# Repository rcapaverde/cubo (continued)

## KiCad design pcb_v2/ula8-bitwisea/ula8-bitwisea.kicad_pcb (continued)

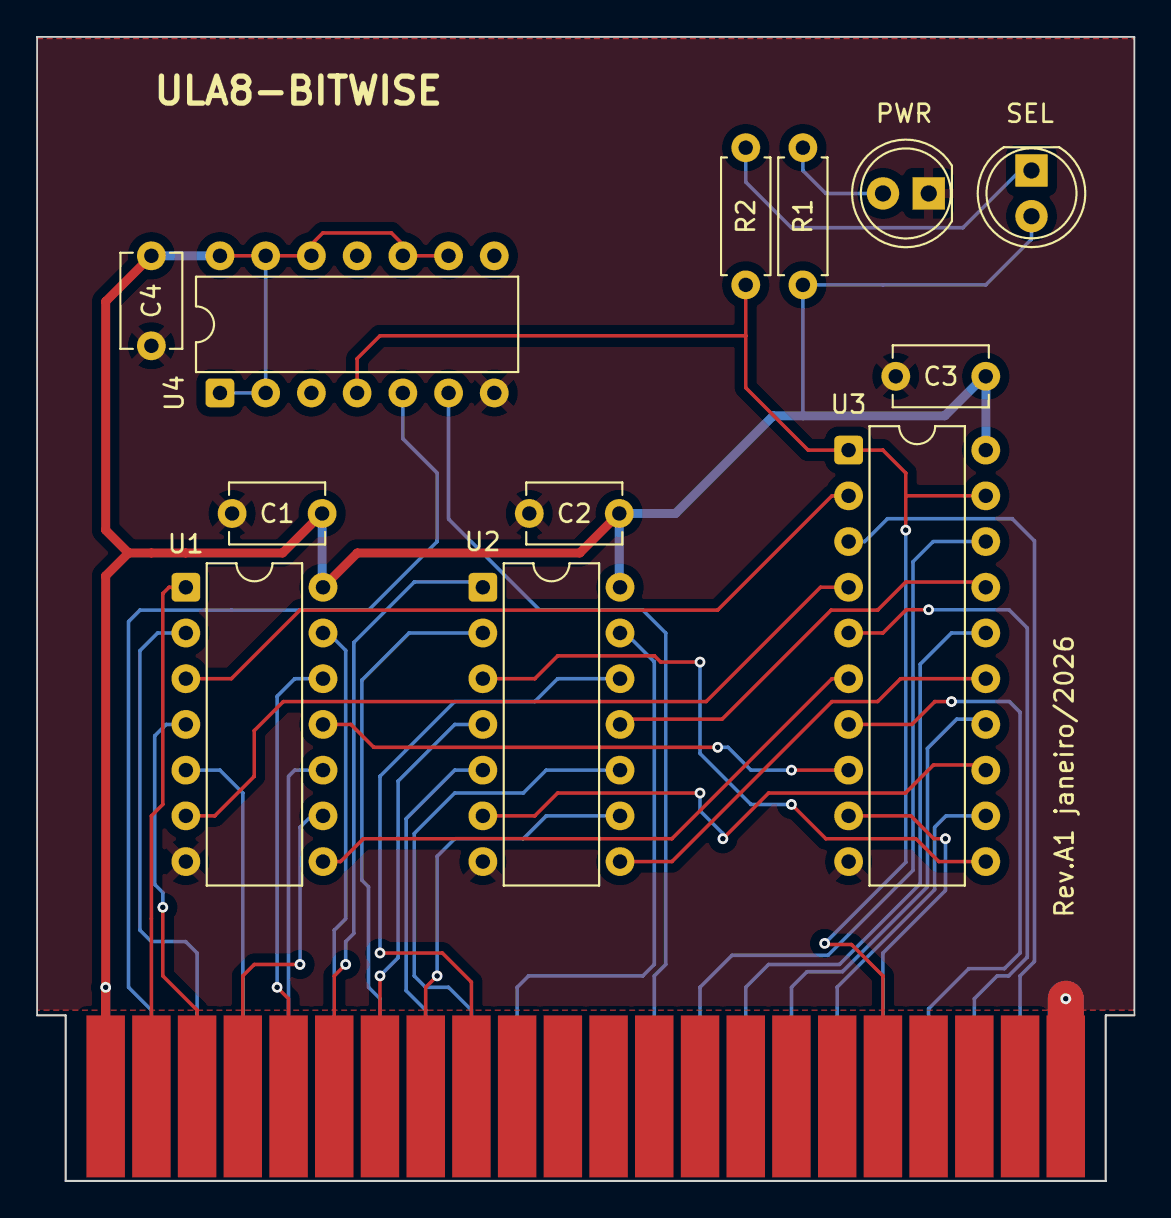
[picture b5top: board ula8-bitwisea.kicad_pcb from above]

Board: 2 copper layers, 61.0 x 63.6 mm, 13 parts (0 on the bottom side), 39 nets.

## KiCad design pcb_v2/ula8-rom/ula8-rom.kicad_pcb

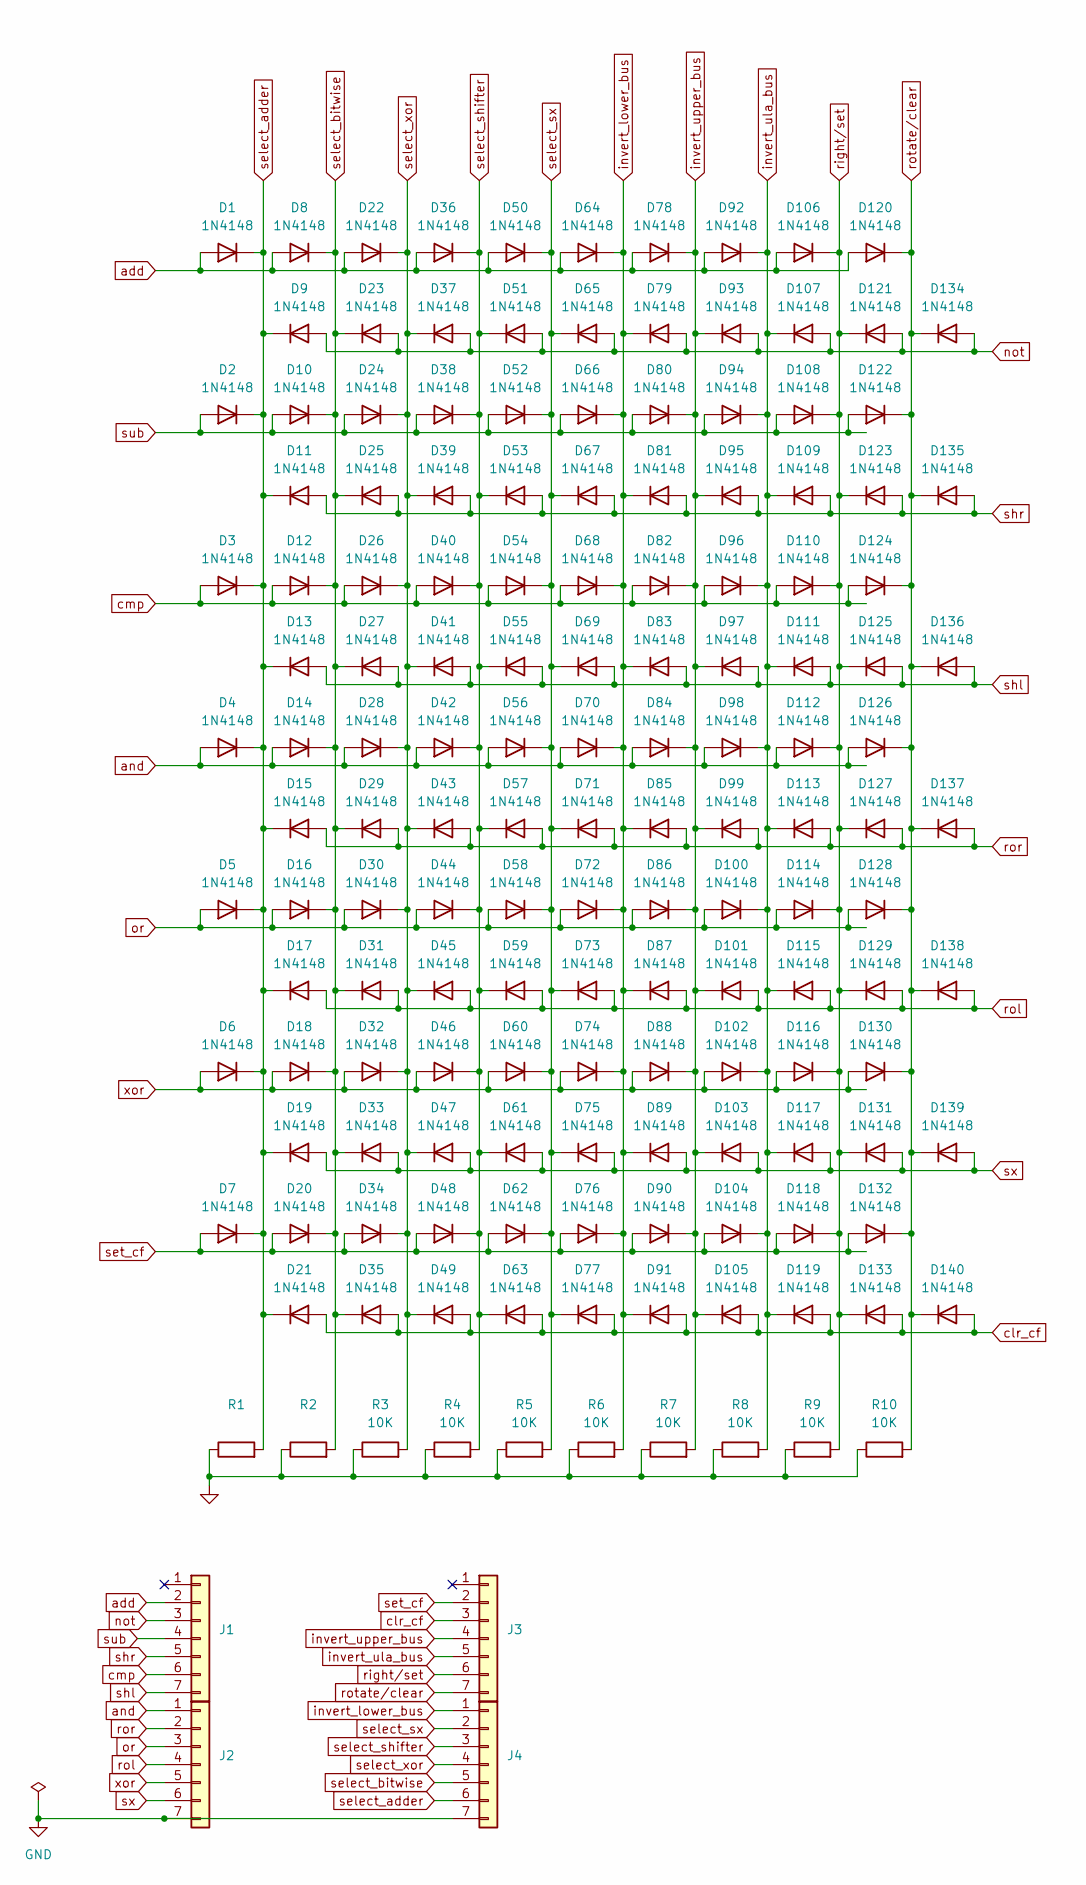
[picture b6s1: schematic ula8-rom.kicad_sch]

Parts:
D1, D2, D3, D4, D5, D6, D7, D8, D9, D10, D11, D12, D13, D14, D15, D16, D17, D18, D19, D20, D21, D22, D23, D24, D25, D26, D27, D28, D29, D30, D31, D32, D33, D34, D35, D36, D37, D38, D39, D40, D41, D42, D43, D44, D45, D46, D47, D48, D49, D50, D51, D52, D53, D54, D55, D56, D57, D58, D59, D60, D61, D62, D63, D64, D65, D66, D67, D68, D69, D70, D71, D72, D73, D74, D75, D76, D77, D78, D79, D80, D81, D82, D83, D84, D85, D86, D87, D88, D89, D90, D91, D92, D93, D94, D95, D96, D97, D98, D99, D100, D101, D102, D103, D104, D105, D106, D107, D108, D109, D110, D111, D112, D113, D114, D115, D116, D117, D118, D119, D120, D121, D122, D123, D124, D125, D126, D127, D128, D129, D130, D131, D132, D133, D134, D135, D136, D137, D138, D139, D140: 1N4148; D_DO-35_SOD27_P7.62mm_Horizontal
J1, J2, J3, J4: (no value)
R1, R2: (no value)
R3, R4, R5, R6, R7, R8, R9, R10: 10K

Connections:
add: D1.2 (A), D8.2 (A), D22.2 (A), D36.2 (A), D50.2 (A), D64.2 (A), D78.2 (A), D92.2 (A), D106.2 (A), D120.2 (A), J1.2
and: D4.2 (A), D14.2 (A), D28.2 (A), D42.2 (A), D56.2 (A), D70.2 (A), D84.2 (A), D98.2 (A), D112.2 (A), D126.2 (A), J2.1
clr_cf: D21.2 (A), D35.2 (A), D49.2 (A), D63.2 (A), D77.2 (A), D91.2 (A), D105.2 (A), D119.2 (A), D133.2 (A), D140.2 (A), J3.3
cmp: D3.2 (A), D12.2 (A), D26.2 (A), D40.2 (A), D54.2 (A), D68.2 (A), D82.2 (A), D96.2 (A), D110.2 (A), D124.2 (A), J1.6
invert_lower_bus: D64.1 (K), D66.1 (K), D68.1 (K), D70.1 (K), D72.1 (K), D74.1 (K), D76.1 (K), D79.1 (K), D81.1 (K), D83.1 (K), D85.1 (K), D87.1 (K), D89.1 (K), D91.1 (K), J4.1, R6.2
invert_ula_bus: D92.1 (K), D94.1 (K), D96.1 (K), D98.1 (K), D100.1 (K), D102.1 (K), D104.1 (K), D107.1 (K), D109.1 (K), D111.1 (K), D113.1 (K), D115.1 (K), D117.1 (K), D119.1 (K), J3.5, R8.2
invert_upper_bus: D78.1 (K), D80.1 (K), D82.1 (K), D84.1 (K), D86.1 (K), D88.1 (K), D90.1 (K), D93.1 (K), D95.1 (K), D97.1 (K), D99.1 (K), D101.1 (K), D103.1 (K), D105.1 (K), J3.4, R7.2
not: D9.2 (A), D23.2 (A), D37.2 (A), D51.2 (A), D65.2 (A), D79.2 (A), D93.2 (A), D107.2 (A), D121.2 (A), D134.2 (A), J1.3
or: D5.2 (A), D16.2 (A), D30.2 (A), D44.2 (A), D58.2 (A), D72.2 (A), D86.2 (A), D100.2 (A), D114.2 (A), D128.2 (A), J2.3
right/set: D106.1 (K), D108.1 (K), D110.1 (K), D112.1 (K), D114.1 (K), D116.1 (K), D118.1 (K), D121.1 (K), D123.1 (K), D125.1 (K), D127.1 (K), D129.1 (K), D131.1 (K), D133.1 (K), J3.6, R9.2
rol: D17.2 (A), D31.2 (A), D45.2 (A), D59.2 (A), D73.2 (A), D87.2 (A), D101.2 (A), D115.2 (A), D129.2 (A), D138.2 (A), J2.4
ror: D15.2 (A), D29.2 (A), D43.2 (A), D57.2 (A), D71.2 (A), D85.2 (A), D99.2 (A), D113.2 (A), D127.2 (A), D137.2 (A), J2.2
rotate/clear: D120.1 (K), D122.1 (K), D124.1 (K), D126.1 (K), D128.1 (K), D130.1 (K), D132.1 (K), D134.1 (K), D135.1 (K), D136.1 (K), D137.1 (K), D138.1 (K), D139.1 (K), D140.1 (K), J3.7, R10.2
select_adder: D1.1 (K), D2.1 (K), D3.1 (K), D4.1 (K), D5.1 (K), D6.1 (K), D7.1 (K), D9.1 (K), D11.1 (K), D13.1 (K), D15.1 (K), D17.1 (K), D19.1 (K), D21.1 (K), J4.6, R1.2
select_bitwise: D8.1 (K), D10.1 (K), D12.1 (K), D14.1 (K), D16.1 (K), D18.1 (K), D20.1 (K), D23.1 (K), D25.1 (K), D27.1 (K), D29.1 (K), D31.1 (K), D33.1 (K), D35.1 (K), J4.5, R2.2
select_shifter: D36.1 (K), D38.1 (K), D40.1 (K), D42.1 (K), D44.1 (K), D46.1 (K), D48.1 (K), D51.1 (K), D53.1 (K), D55.1 (K), D57.1 (K), D59.1 (K), D61.1 (K), D63.1 (K), J4.3, R4.2
select_sx: D50.1 (K), D52.1 (K), D54.1 (K), D56.1 (K), D58.1 (K), D60.1 (K), D62.1 (K), D65.1 (K), D67.1 (K), D69.1 (K), D71.1 (K), D73.1 (K), D75.1 (K), D77.1 (K), J4.2, R5.2
select_xor: D22.1 (K), D24.1 (K), D26.1 (K), D28.1 (K), D30.1 (K), D32.1 (K), D34.1 (K), D37.1 (K), D39.1 (K), D41.1 (K), D43.1 (K), D45.1 (K), D47.1 (K), D49.1 (K), J4.4, R3.2
set_cf: D7.2 (A), D20.2 (A), D34.2 (A), D48.2 (A), D62.2 (A), D76.2 (A), D90.2 (A), D104.2 (A), D118.2 (A), D132.2 (A), J3.2
shl: D13.2 (A), D27.2 (A), D41.2 (A), D55.2 (A), D69.2 (A), D83.2 (A), D97.2 (A), D111.2 (A), D125.2 (A), D136.2 (A), J1.7
shr: D11.2 (A), D25.2 (A), D39.2 (A), D53.2 (A), D67.2 (A), D81.2 (A), D95.2 (A), D109.2 (A), D123.2 (A), D135.2 (A), J1.5
sub: D2.2 (A), D10.2 (A), D24.2 (A), D38.2 (A), D52.2 (A), D66.2 (A), D80.2 (A), D94.2 (A), D108.2 (A), D122.2 (A), J1.4
sx: D19.2 (A), D33.2 (A), D47.2 (A), D61.2 (A), D75.2 (A), D89.2 (A), D103.2 (A), D117.2 (A), D131.2 (A), D139.2 (A), J2.6
xor: D6.2 (A), D18.2 (A), D32.2 (A), D46.2 (A), D60.2 (A), D74.2 (A), D88.2 (A), D102.2 (A), D116.2 (A), D130.2 (A), J2.5

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
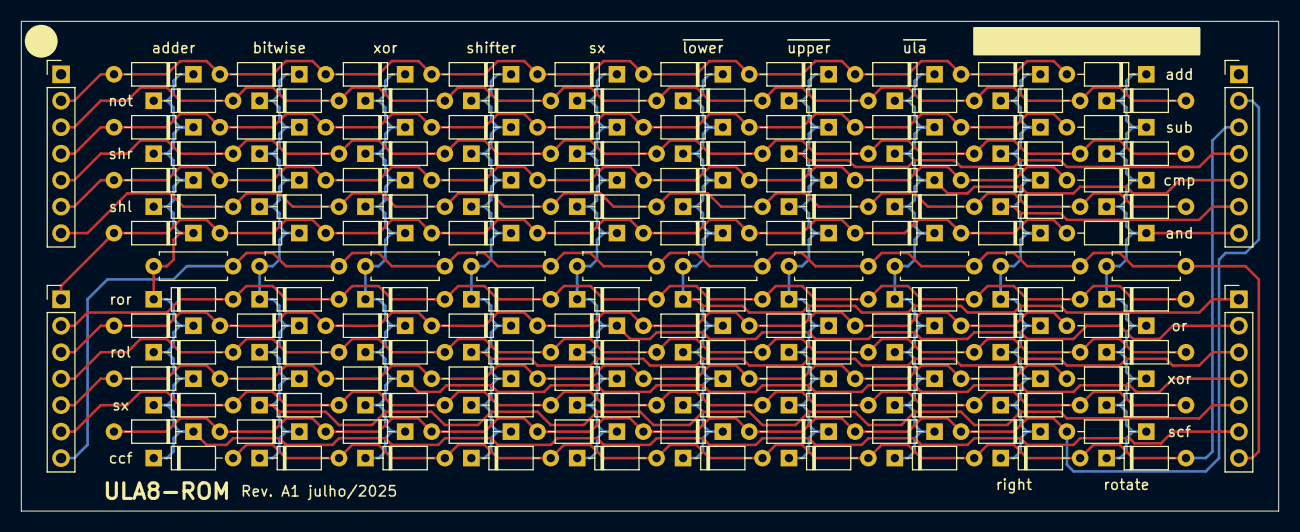
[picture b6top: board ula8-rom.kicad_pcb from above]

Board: 2 copper layers, 120.6 x 47.0 mm, 154 parts (0 on the bottom side), 25 nets.

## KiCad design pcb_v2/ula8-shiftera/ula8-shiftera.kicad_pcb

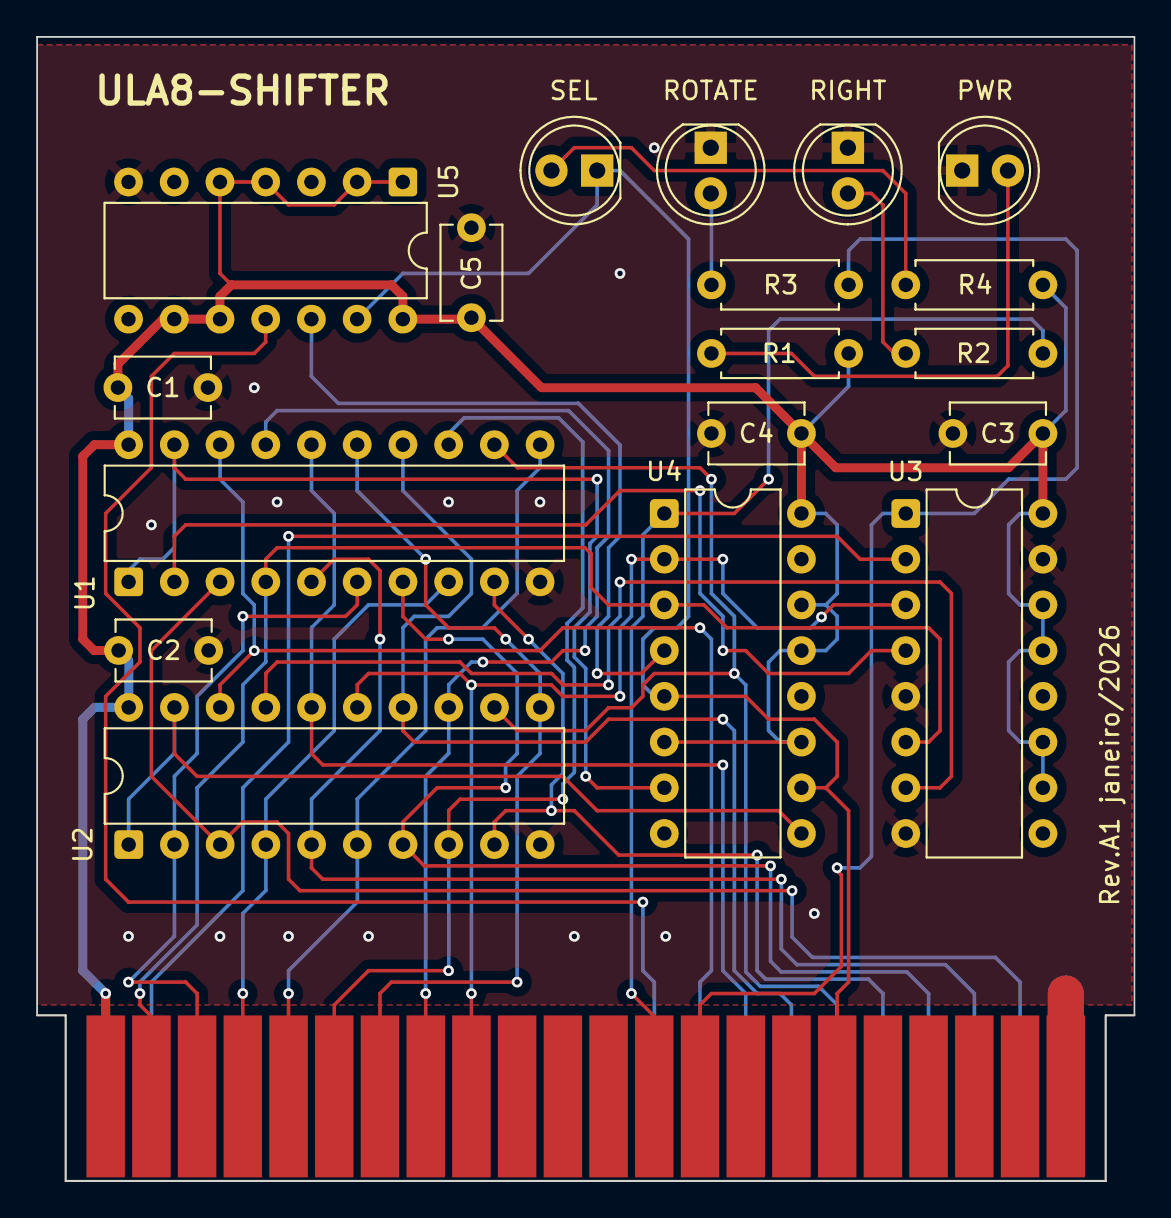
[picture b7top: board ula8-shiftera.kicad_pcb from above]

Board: 2 copper layers, 61.0 x 63.5 mm, 19 parts (0 on the bottom side), 32 nets.

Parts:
C1, C2, C3, C4, C5: 100nF; C_Disc_D5.1mm_W3.2mm_P5.00mm
D1, D2, D3, D4: LED; LED_D5.0mm
J1: ula8a; edge-connector-44
R1, R2, R3, R4: 1K; R_Axial_DIN0207_L6.3mm_D2.5mm_P7.62mm_Horizontal
U1, U2: 74LS244; DIP-20_W7.62mm
U3, U4: 74LS157; DIP-16_W7.62mm
U5: 74LS125; DIP-14_W7.62mm

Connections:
+5V: C1.2, C2.2, C3.2, C4.2, C5.2, J1.1, J1.23, R1.1, R4.1, U1.20 (VCC), U2.20 (VCC), U3.10 (I1c), U3.11 (I0c), U3.13 (I1d), U3.14 (I0d), U3.16 (VCC), U4.6 (I1b), U4.11 (I0c), U4.13 (I1d), U4.14 (I0d), U4.16 (VCC), U5.1, U5.2, U5.4, U5.5, U5.9, U5.10, U5.14 (VCC)
GND: C1.1, C2.1, C3.1, C4.1, C5.1, D1.1 (K), D2.1 (K), D3.1 (K), J1.22, J1.44, U1.10 (GND), U2.10 (GND), U3.5 (I0b), U3.8 (GND), U3.15 (E), U4.8 (GND), U4.15 (E), U5.7 (GND)
unnamed: D1.2 (A), R1.2
unnamed: D2.2 (A), R2.2
unnamed: D3.2 (A), R3.2
unnamed: D4.2 (A), R4.2
unnamed: U1.2 (I0a), U3.4 (Za)
unnamed: U2.17 (I3b), U3.7 (Zb)
unnamed: U4.4 (Za), U5.12
carry_in: J1.24, U3.2 (I0a)
carry_out: J1.35, U5.11
lower_bus0: J1.2, U1.4 (I1a), U3.6 (I1b), U4.3 (I1a)
lower_bus1: J1.3, U1.6 (I2a), U2.2 (I0a)
lower_bus2: J1.4, U1.8 (I3a), U2.4 (I1a)
lower_bus3: J1.5, U1.11 (I0b), U2.6 (I2a)
lower_bus4: J1.6, U1.13 (I1b), U2.8 (I3a)
lower_bus5: J1.7, U1.15 (I2b), U2.11 (I0b)
lower_bus6: J1.8, U1.17 (I3b), U2.13 (I1b)
lower_bus7: J1.9, U2.15 (I2b), U3.3 (I1a), U4.2 (I0a)
option_right: J1.13, R2.1, U4.1 (S)
option_rotate: J1.14, R3.1, U3.1 (S)
ula_bus0: J1.36, U1.18 (O0a), U2.18 (O0a)
ula_bus1: J1.37, U1.16 (O1a), U2.16 (O1a)
ula_bus2: J1.38, U1.14 (O2a), U2.14 (O2a)
ula_bus3: J1.39, U1.12 (O3a), U2.12 (O3a)
ula_bus4: J1.40, U1.9 (O0b), U2.9 (O0b)
ula_bus5: J1.41, U1.7 (O1b), U2.7 (O1b)
ula_bus6: J1.42, U1.5 (O2b), U2.5 (O2b)
ula_bus7: J1.43, U1.3 (O3b), U2.3 (O3b)
~select: D4.1 (K), J1.17, U4.5 (I0b), U4.10 (I1c), U5.13
~shift_left: U1.1 (OEa), U1.19 (OEb), U4.7 (Zb)
~shift_right: U2.1 (OEa), U2.19 (OEb), U4.9 (Zc)

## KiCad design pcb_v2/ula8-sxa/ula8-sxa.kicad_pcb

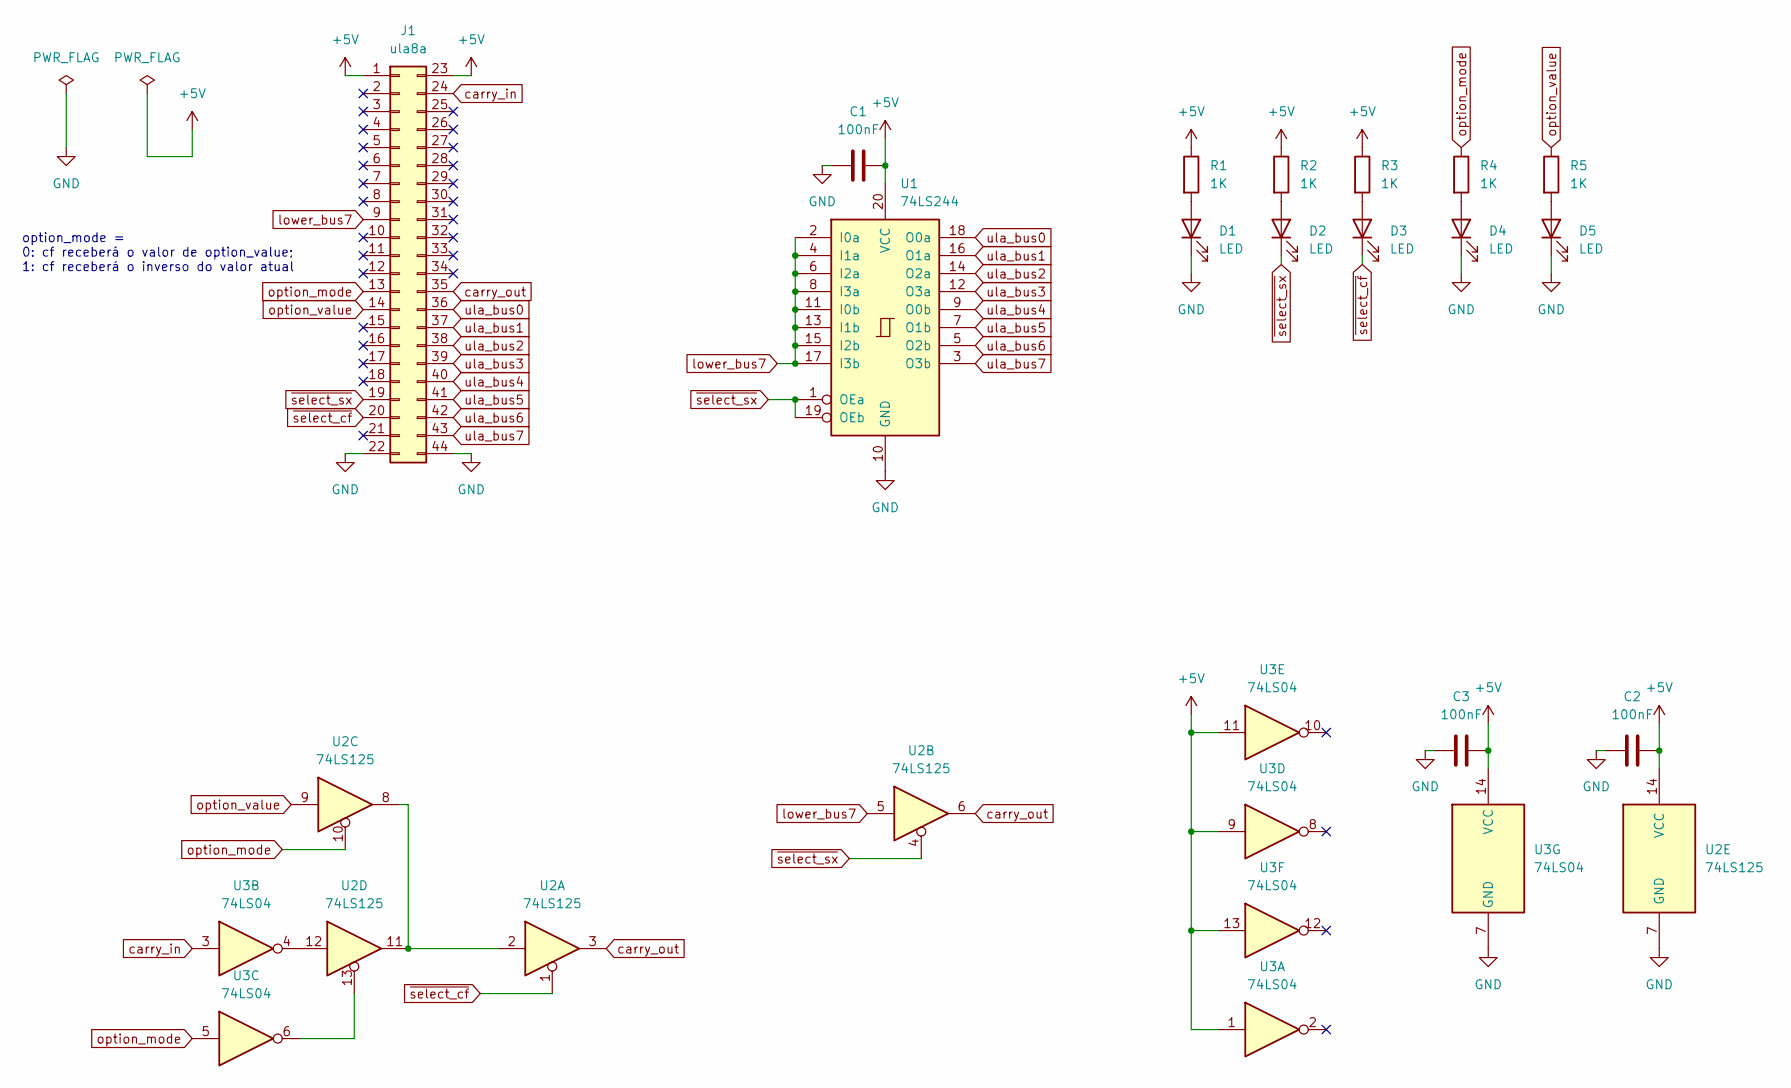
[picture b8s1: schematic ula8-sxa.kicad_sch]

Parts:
C1, C2, C3: 100nF; C_Disc_D5.1mm_W3.2mm_P5.00mm
D1, D2, D3, D4, D5: LED; LED_D5.0mm
J1: ula8a; edge-connector-44
R1, R2, R3, R4, R5: 1K; R_Axial_DIN0207_L6.3mm_D2.5mm_P7.62mm_Horizontal
U1: 74LS244; DIP-20_W7.62mm
U2: 74LS125; DIP-14_W7.62mm
U3: 74LS04; DIP-14_W7.62mm

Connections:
+5V: C1.2, C2.2, C3.2, J1.1, J1.23, R1.1, R2.1, R3.1, U1.20 (VCC), U2.14 (VCC), U3.1, U3.9, U3.11, U3.13, U3.14 (VCC)
GND: C1.1, C2.1, C3.1, D1.1 (K), D4.1 (K), D5.1 (K), J1.22, J1.44, U1.10 (GND), U2.7 (GND), U3.7 (GND)
unnamed: D1.2 (A), R1.2
unnamed: D2.2 (A), R2.2
unnamed: D3.2 (A), R3.2
unnamed: D4.2 (A), R4.2
unnamed: D5.2 (A), R5.2
unnamed: U2.2, U2.8, U2.11
unnamed: U2.12, U3.4
unnamed: U2.13, U3.6
carry_in: J1.24, U3.3
carry_out: J1.35, U2.3, U2.6
lower_bus7: J1.9, U1.2 (I0a), U1.4 (I1a), U1.6 (I2a), U1.8 (I3a), U1.11 (I0b), U1.13 (I1b), U1.15 (I2b), U1.17 (I3b), U2.5
option_mode: J1.13, R4.1, U2.10, U3.5
option_value: J1.14, R5.1, U2.9
ula_bus0: J1.36, U1.18 (O0a)
ula_bus1: J1.37, U1.16 (O1a)
ula_bus2: J1.38, U1.14 (O2a)
ula_bus3: J1.39, U1.12 (O3a)
ula_bus4: J1.40, U1.9 (O0b)
ula_bus5: J1.41, U1.7 (O1b)
ula_bus6: J1.42, U1.5 (O2b)
ula_bus7: J1.43, U1.3 (O3b)
~select_cf: D3.1 (K), J1.20, U2.1
~select_sx: D2.1 (K), J1.19, U1.1 (OEa), U1.19 (OEb), U2.4

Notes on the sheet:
option_mode = 0: cf receberá o valor de option_value; 1: cf receberá o inverso do valor atual

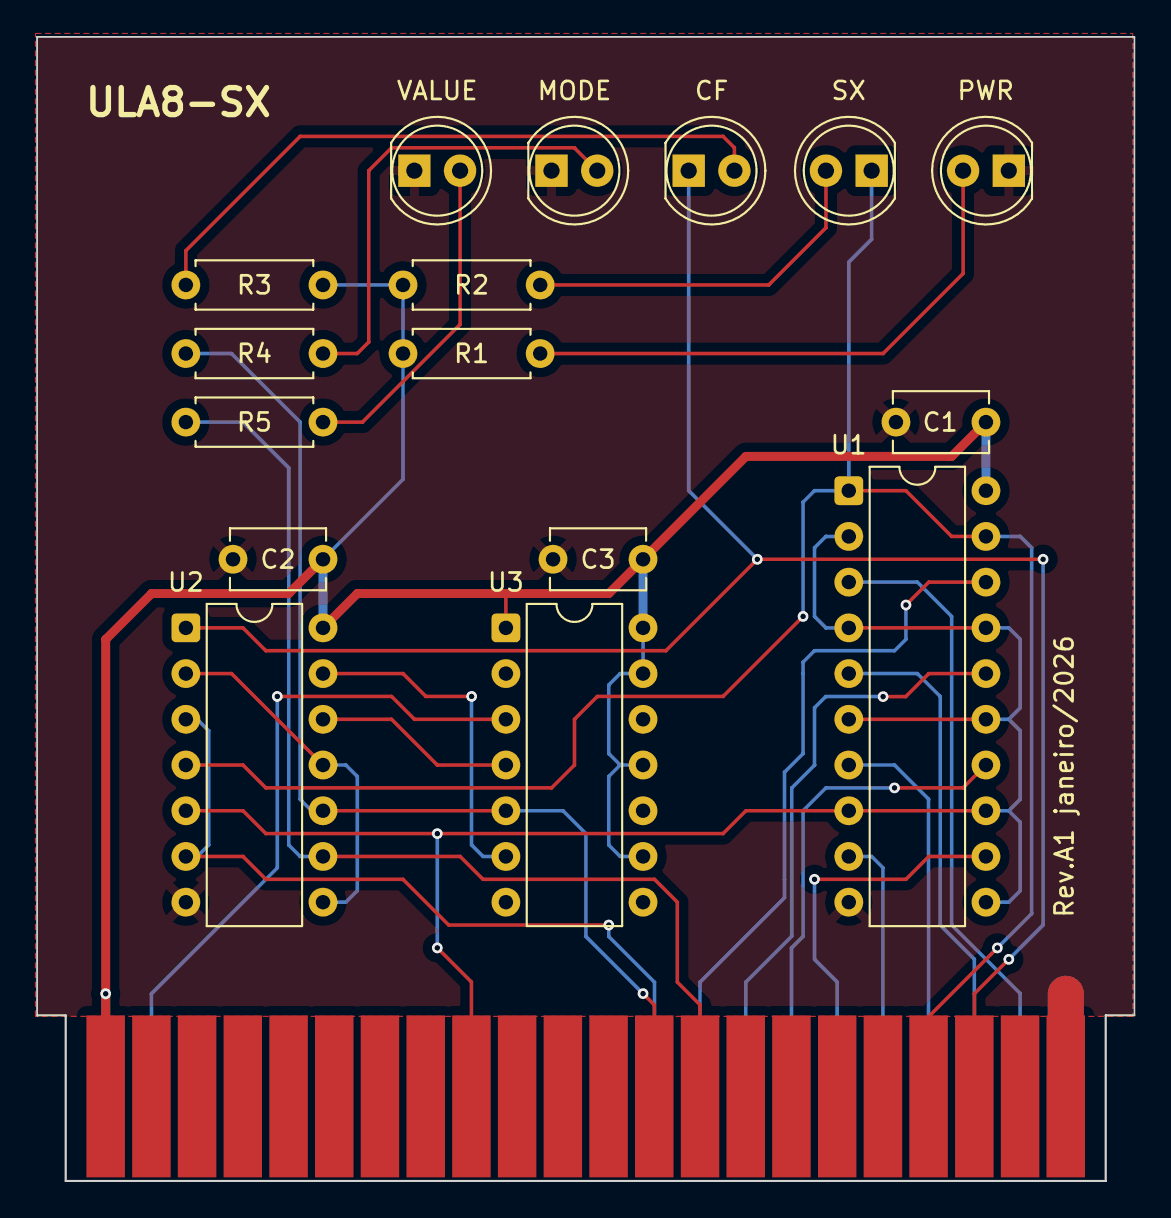
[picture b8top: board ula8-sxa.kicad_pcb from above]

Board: 2 copper layers, 61.0 x 63.5 mm, 17 parts (0 on the bottom side), 25 nets.
